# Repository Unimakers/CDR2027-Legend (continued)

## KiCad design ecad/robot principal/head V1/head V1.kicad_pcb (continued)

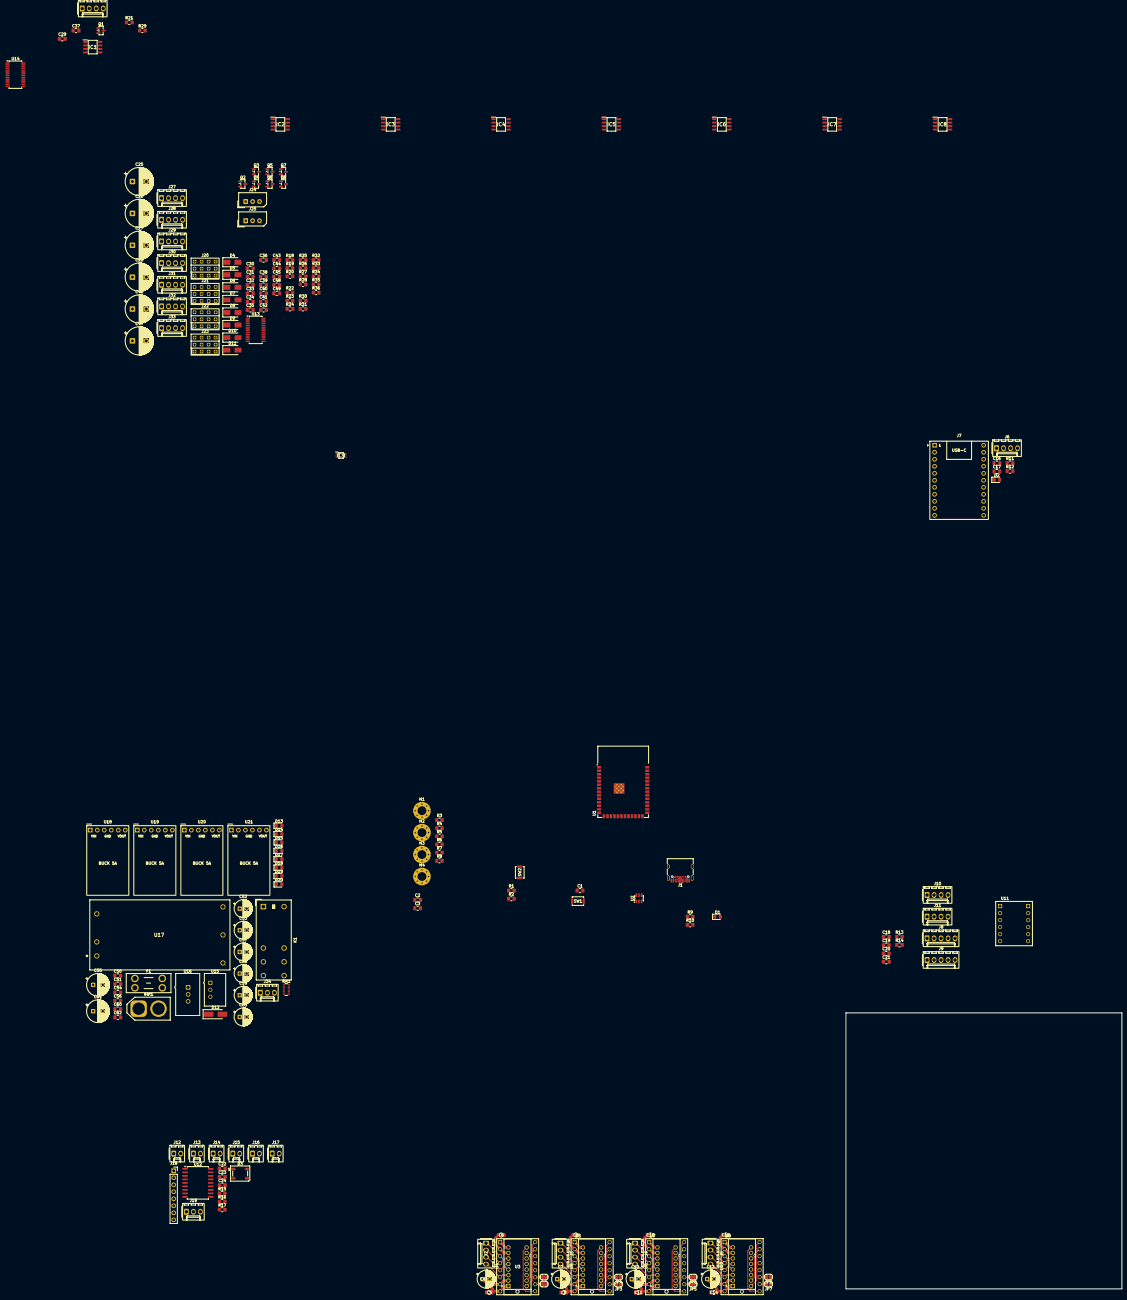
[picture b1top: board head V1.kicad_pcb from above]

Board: 4 copper layers, 100.0 x 100.0 mm, 209 parts (0 on the bottom side), 147 nets.

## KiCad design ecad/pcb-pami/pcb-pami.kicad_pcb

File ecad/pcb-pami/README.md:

# PCBete

Création d'un PCB pour la robotique.

## Objectif :

Carte électronique ESP32-S3-WROOM-U1 permettant : 
- 2 NEMA 17 (28V 2A max), 2 drivers TMC2209
- 2 moteurs DC (3 à 20V 3A max)
- 2 servomoteurs (5V)
- 4 Capteurs TOF VL53L0X (I2C)
- 2 capteurs AS5600 (I2C)
- 1 écran LCD TFT  (SPI) 
- 1 module radio RFM69HCW (SPI)
- LiDAR 5V (UART0)
- LED Neopixel + sa guirlande (60mA/LED)
- Récupération tension d'alimentation (0 à 23V environ avec le pont 200k/33k soudé ; la plage dépend des résistances réellement soudées, voir `fw/include/pamiboard.h`)
- Coopération Master/Slave avec Luckfox Pico Mini B (UART1)
- Bouton d'arrêt d'urgence de puissance (30V 12A max)
- Bouton d'équipe (jaune/bleu)
- Tirette de lancement

## Alimentation

Alimentation possible via PowerBank avec 5V/3A vers la carte en Type-C vers Type-C et/ou batterie LiPo 12V (20V max, si pas driver DC soudé 28V max)

## Luckfox

Micro ordinateur utilisant un noyau Linux capable d'executer du Python cadencé à 1.2Ghz. Afin de décharger l'ESP32-S3 des calculs lourds (path finding, trajctory planner, etc). Il se fixe en direct sur le PCB, se reliant ainsi en UART1 avec l'ESP32 permettant la communication.

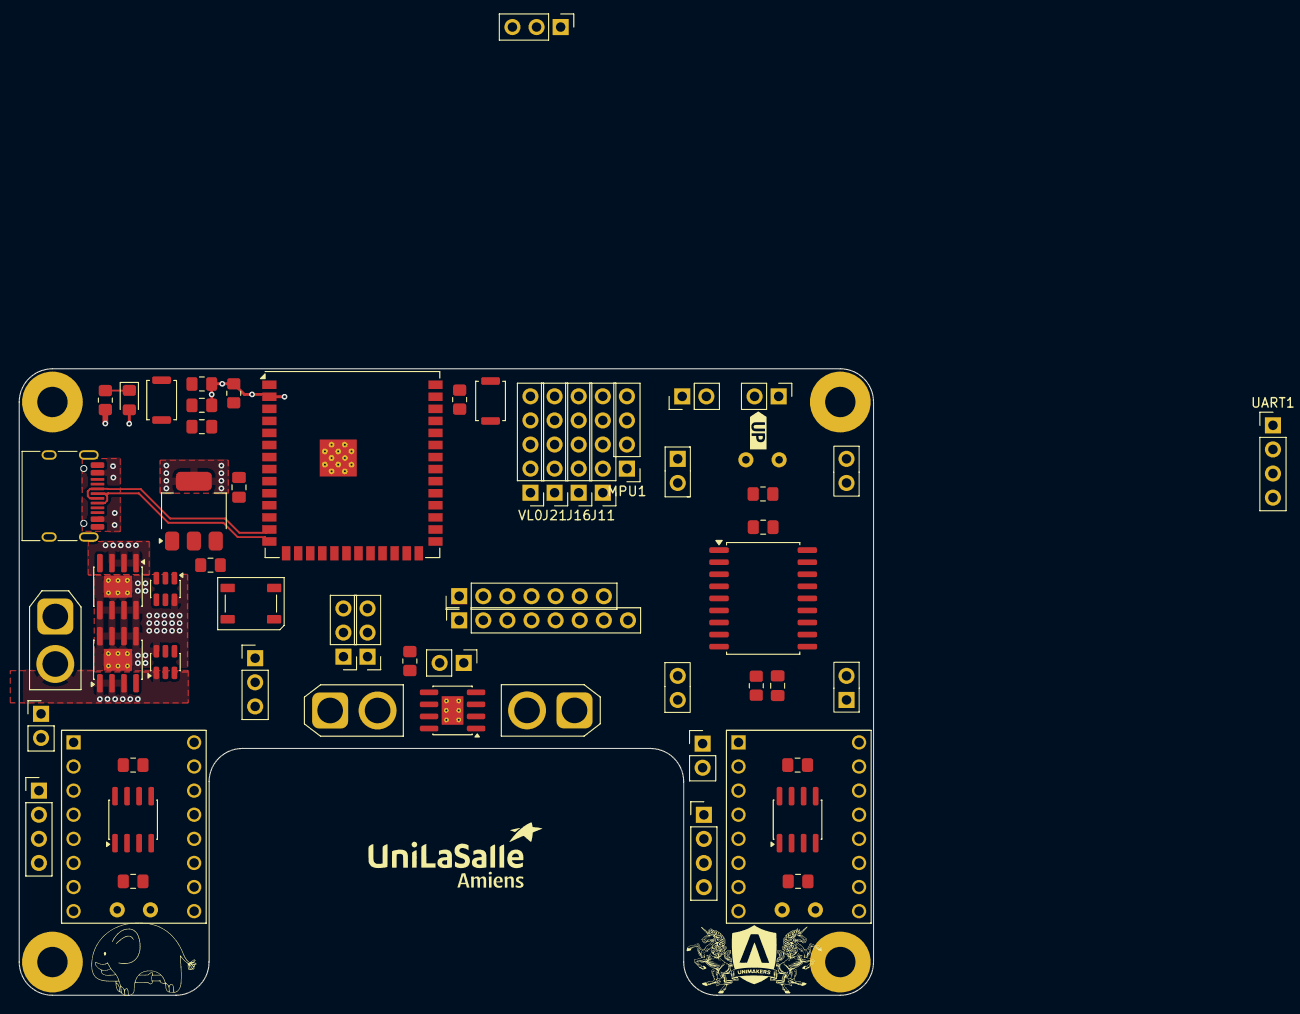
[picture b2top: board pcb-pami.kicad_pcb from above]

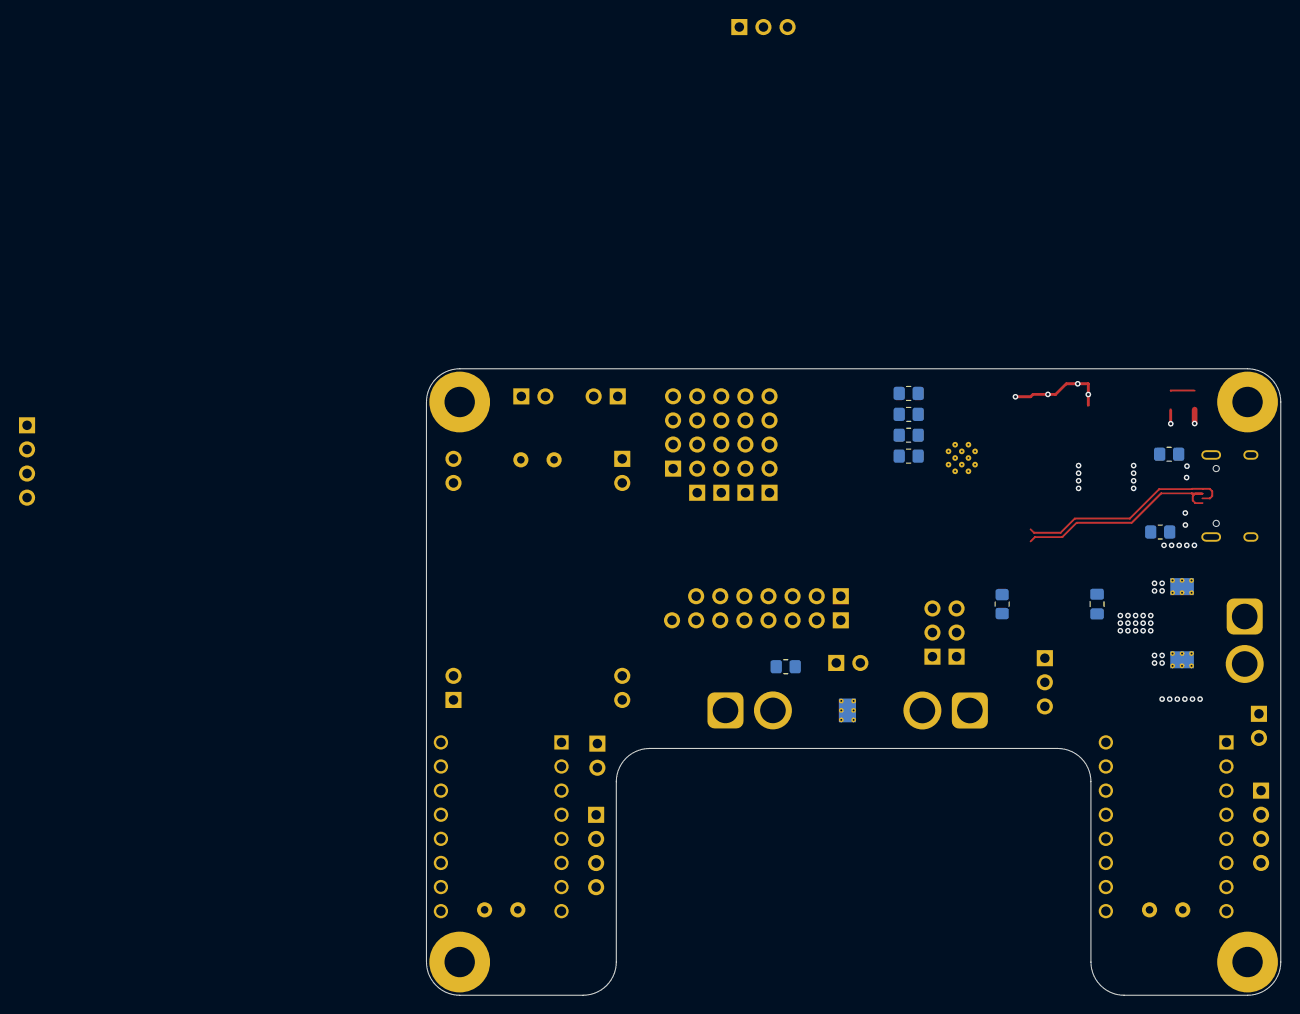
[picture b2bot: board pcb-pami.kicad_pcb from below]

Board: 4 copper layers, 90.0 x 66.0 mm, 75 parts (9 on the bottom side), 65 nets.

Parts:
AO4407A1, AO4407A2, AO4407A4: PMOS; SOIC-8-1EP_3.9x4.9mm_P1.27mm_EP2.29x3mm_ThermalVias
C2: 1uF; C_0805_2012Metric_Pad1.18x1.45mm_HandSolder
C4, C6: 100u; C_Radial_D8.0mm_H11.5mm_P3.50mm
C5, C7, C9: 10uF; C_0805_2012Metric_Pad1.18x1.45mm_HandSolder
C10: 0.1uF; C_0805_2012Metric_Pad1.18x1.45mm_HandSolder
C11: 470u; C_Radial_D8.0mm_H11.5mm_P3.50mm
C12, C13, C16, C17, C18, C19, C20, C21: 100nF; C_0805_2012Metric_Pad1.18x1.45mm_HandSolder
D1: LED_0805_2012Metric_Pad1.15x1.40mm_HandSolder
D6: WS2812B; LED_WS2812B_PLCC4_5.0x5.0mm_P3.2mm
H1, H2, H3, H4: MountingHole_Pad; MountingHole_3.2mm_M3_Pad
J1: USB_C_Receptacle_USB2.0_16P; USB_C_Receptacle_HRO_TYPE-C-31-M-12
J2, J4: Conn_01x11_Socket; PinSocket_1x11_P2.54mm_Vertical
J3: Conn_01x08_Socket; PinSocket_1x08_P2.54mm_Vertical
J5, J7, J9, J12, J27: Conn_01x02_Pin; PinHeader_1x02_P2.54mm_Vertical
J6, J10, J15: Conn_01x02_Pin; AMASS_XT30U-F_1x02_P5.0mm_Vertical
J8, J23, J26: Conn_01x03_Pin; PinHeader_1x03_P2.54mm_Vertical
J11, J16, J21: Conn_01x05_Pin; PinHeader_1x05_P2.54mm_Vertical
J14, J22: Conn_01x04_Pin; PinHeader_1x04_P2.54mm_Vertical
J17: Conn_01x07_Pin; PinHeader_1x07_P2.54mm_Vertical
MPU1: Conn_01x04_Pin; PinHeader_1x04_P2.54mm_Vertical
R1, R10, R13: 10k; R_0805_2012Metric_Pad1.20x1.40mm_HandSolder
R2, R3: 5.1k; R_0805_2012Metric_Pad1.20x1.40mm_HandSolder
R4: 330; R_0805_2012Metric_Pad1.20x1.40mm_HandSolder
R5, R6, R7, R8: 4.7k; R_0805_2012Metric_Pad1.20x1.40mm_HandSolder
R12: 470; R_0805_2012Metric_Pad1.20x1.40mm_HandSolder
R14: 270k; R_0805_2012Metric_Pad1.20x1.40mm_HandSolder
R15: 33k; R_0805_2012Metric_Pad1.20x1.40mm_HandSolder
SW1, SW2: SW_Push; SW_Push_SPST_NO_Alps_SKRK
U1, U5: SOIC-8_3.9x4.9mm_P1.27mm
U2, U3: LTC4412xS6; TSOT-23-6
U4: AMS1117-3.3 (UMW); SOT-223-3_TabPin2
U6: ESP32-S3-WROOM-1; ESP32-S3-WROOM-1U
U8, U9: TMC2209_SILENTSTEPSTICK; MODULE_TMC2209_SILENTSTEPSTICK
U10: MCP23008-xSO; SOIC-18W_7.5x11.6mm_P1.27mm
UART0: Conn_01x03_Pin; PinHeader_1x03_P2.54mm_Vertical
UART1: Conn_01x04_Pin; PinHeader_1x04_P2.54mm_Vertical
VL0: Conn_01x05_Pin; PinHeader_1x05_P2.54mm_Vertical
kibuzzard-6A6F48EA: G***; kibuzzard-6A6F48EA

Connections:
3V3: C7.1, C9.1, C10.1, C17.1, D1.2 (A), J3.2, J3.8, J17.2, R1.1, R5.1, R6.1, R7.1, R8.1, R10.1, U4.2 (VO), U6.2 (3V3), U8.2 (VIO), U9.2 (VIO), U10.6 (~RESET), U10.18 (VDD)
BAU+: AO4407A4.4 (G), J9.1, R13.2
BOOT: R10.2, SW1.2, U6.27 (IO0)
CS: J3.7, U6.32 (IO39)
CS2: J17.6, U6.37 (TXD0)
DC: J3.6, U6.30 (IO37)
DIR2: U6.10 (IO17), U8.9 (DIR)
EN: U8.16 (~EN), U9.16 (~EN), U10.13 (GP3)
ESP32_EN: C2.1, R1.2, SW2.2, U6.3 (EN)
GND: C2.2, C4.2, C5.2, C6.2, C7.2, C9.2, C10.2, C11.2, C12.2, C13.2, C16.2, C17.2, C19.2, C21.2, D6.3 (VSS), H1.1 (1_1), H2.1 (1_1), H3.1 (1_1), H4.1 (1_1), J1.A1 (GND), J1.A12 (GND), J1.B1 (GND), J1.B12 (GND), J2.10, J3.1, J4.2, J5.2, J6.1, J7.2, J8.3, J9.2, J10.1, J11.4, J15.1, J16.4, J17.1, J21.4, J23.1, J26.1, MPU1.3, R2.2, R3.2, R4.2, R15.1, SW1.1, SW2.1, U1.3 (GND), U2.2 (GND), U2.3 (CTL), U3.2 (GND), U3.3 (CTL), U4.1 (GND), U5.3 (GND), U6.1 (GND), U6.40 (GND), U6.41 (GND), U8.1 (GND), U8.7 (GND), U9.1 (GND), U9.7 (GND), U10.3 (A2), U10.4 (A1), U10.5 (A0), U10.9 (VSS), UART0.1, UART1.1, VL0.4
IRQ: J17.7, U6.33 (IO40)
LAUNCHPULL: J7.1, U10.12 (GP2)
M1+: C18.1, J12.1, U1.5 (Fo), U1.6 (Fo)
M1-: C18.2, J12.2, U1.7 (Bo), U1.8 (Bo)
M1_IN1: U1.2 (FI), U6.8 (IO15)
M1_IN2: U1.1 (BI), U6.7 (IO7)
M2+: C20.1, J27.1, U5.5 (Fo), U5.6 (Fo)
M2-: C20.2, J27.2, U5.7 (Bo), U5.8 (Bo)
M2_IN1: U5.2 (FI), U6.6 (IO6)
M2_IN2: U5.1 (BI), U6.5 (IO5)
MISO: J17.5, U6.31 (IO38)
MOSI: J3.4, J17.4, U6.29 (IO36)
MOTORB1: J14.1, U8.3 (M1B)
MOTORB2: J14.2, U8.4 (M1A)
MOTORB3: J14.3, U8.5 (M2A)
MOTORB4: J14.4, U8.6 (M2B)
MOTORC1: J22.1, U9.3 (M1B)
MOTORC2: J22.2, U9.4 (M1A)
MOTORC3: J22.3, U9.5 (M2A)
MOTORC4: J22.4, U9.6 (M2B)
MS1: U6.24 (IO47), U8.15 (MS1), U9.15 (MS1)
MS2: U6.23 (IO21), U8.14 (MS2), U9.14 (MS2)
NEOPIXEL: R12.1, U6.25 (IO48)
NEOPIXEL+: D6.2 (DOUT), J8.2
unnamed: AO4407A1.4 (G), U2.5 (GATE)
unnamed: AO4407A2.4 (G), U3.5 (GATE)
unnamed: D1.1 (K), R4.1
unnamed: D6.4 (DIN), R12.2
unnamed: J1.A5 (CC1), R3.1
unnamed: J1.B5 (CC2), R2.1
RST: J3.5, U10.10 (GP0)
SCL1: J11.3, MPU1.2, R5.2, U6.39 (IO1), VL0.3
SCL2: J16.3, J21.3, R7.2, U6.35 (IO42), U10.1 (SCL)
SCLK: J3.3, J17.3, U6.28 (IO35)
SDA1: J11.2, MPU1.1, R6.2, U6.38 (IO2), VL0.2
SDA2: J16.2, J21.2, R8.2, U6.34 (IO41), U10.2 (SDA)
SERVO0: J26.3, U6.17 (IO9)
SERVO1: J23.3, U6.18 (IO10)
STEP2: U6.9 (IO16), U8.10 (STEP)
TEAM_BTN: J5.1, U10.11 (GP1)
UART0_RX-: U6.36 (RXD0), UART0.2
UART1_RX-: J2.1, U6.11 (IO18), UART1.3
UART1_TX+: J2.2, U6.12 (IO8), UART1.2
USB_N: J1.A7 (D-), J1.B7 (D-), U6.13 (IO19)
USB_P: J1.A6 (D+), J1.B6 (D+), U6.14 (IO20)
VCC_5V_BUCK: AO4407A2.1 (S), AO4407A2.2 (S), AO4407A2.3 (S), J15.2, U3.1 (VIN)
VCC_5V_GLOBAL: AO4407A1.5 (D), AO4407A1.6 (D), AO4407A1.7 (D), AO4407A1.8 (D), AO4407A1.9 (D), AO4407A2.5 (D), AO4407A2.6 (D), AO4407A2.7 (D), AO4407A2.8 (D), AO4407A2.9 (D), C5.1, C11.1, C12.1, C21.1, D6.1 (VDD), J4.1, J8.1, J11.5, J16.5, J21.5, J23.2, J26.2, MPU1.4, U2.6 (SENSE), U3.6 (SENSE), U4.3 (VI), UART0.3, UART1.4, VL0.5
VCC_5V_USB: AO4407A1.1 (S), AO4407A1.2 (S), AO4407A1.3 (S), J1.A4 (VBUS), J1.A9 (VBUS), J1.B4 (VBUS), J1.B9 (VBUS), U2.1 (VIN)
VCC_12V: AO4407A4.5 (D), AO4407A4.6 (D), AO4407A4.7 (D), AO4407A4.8 (D), AO4407A4.9 (D), C4.1, C6.1, C16.1, C19.1, J10.2, R14.2, U1.4 (VCC), U5.4 (VCC), U8.8 (VM), U9.8 (VM)
VCC_12V_IN: AO4407A4.1 (S), AO4407A4.2 (S), AO4407A4.3 (S), J6.2, R13.1
VCC_CALC: C13.1, R14.1, R15.2, U6.4 (IO4)
XSHUT0: U10.17 (GP7), VL0.1
XSHUT1: J11.1, U10.16 (GP6)
XSHUT2: J16.1, U10.15 (GP5)
XSHUT3: J21.1, U10.14 (GP4)
